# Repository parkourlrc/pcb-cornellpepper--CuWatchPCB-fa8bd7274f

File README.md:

# Pepper-V2
V2 pepper PCB test

## Changes for Rev-3
- Replace the SWD and SWCLK on J7 with some I2C and UART capable GPIOs from Pico. The SWD and SWCLK weren't connected in Rev2 the way I thought they would be
- Replace TMP36 temperature sensor with a TMP235A (similar but cheaper)
- add ability to turn off SiPM 30V from Pico
- make test poinst 1.2mm in diameter (were 0.7mm)
- add logos (woo hoo) and CPERL/CLASSE names

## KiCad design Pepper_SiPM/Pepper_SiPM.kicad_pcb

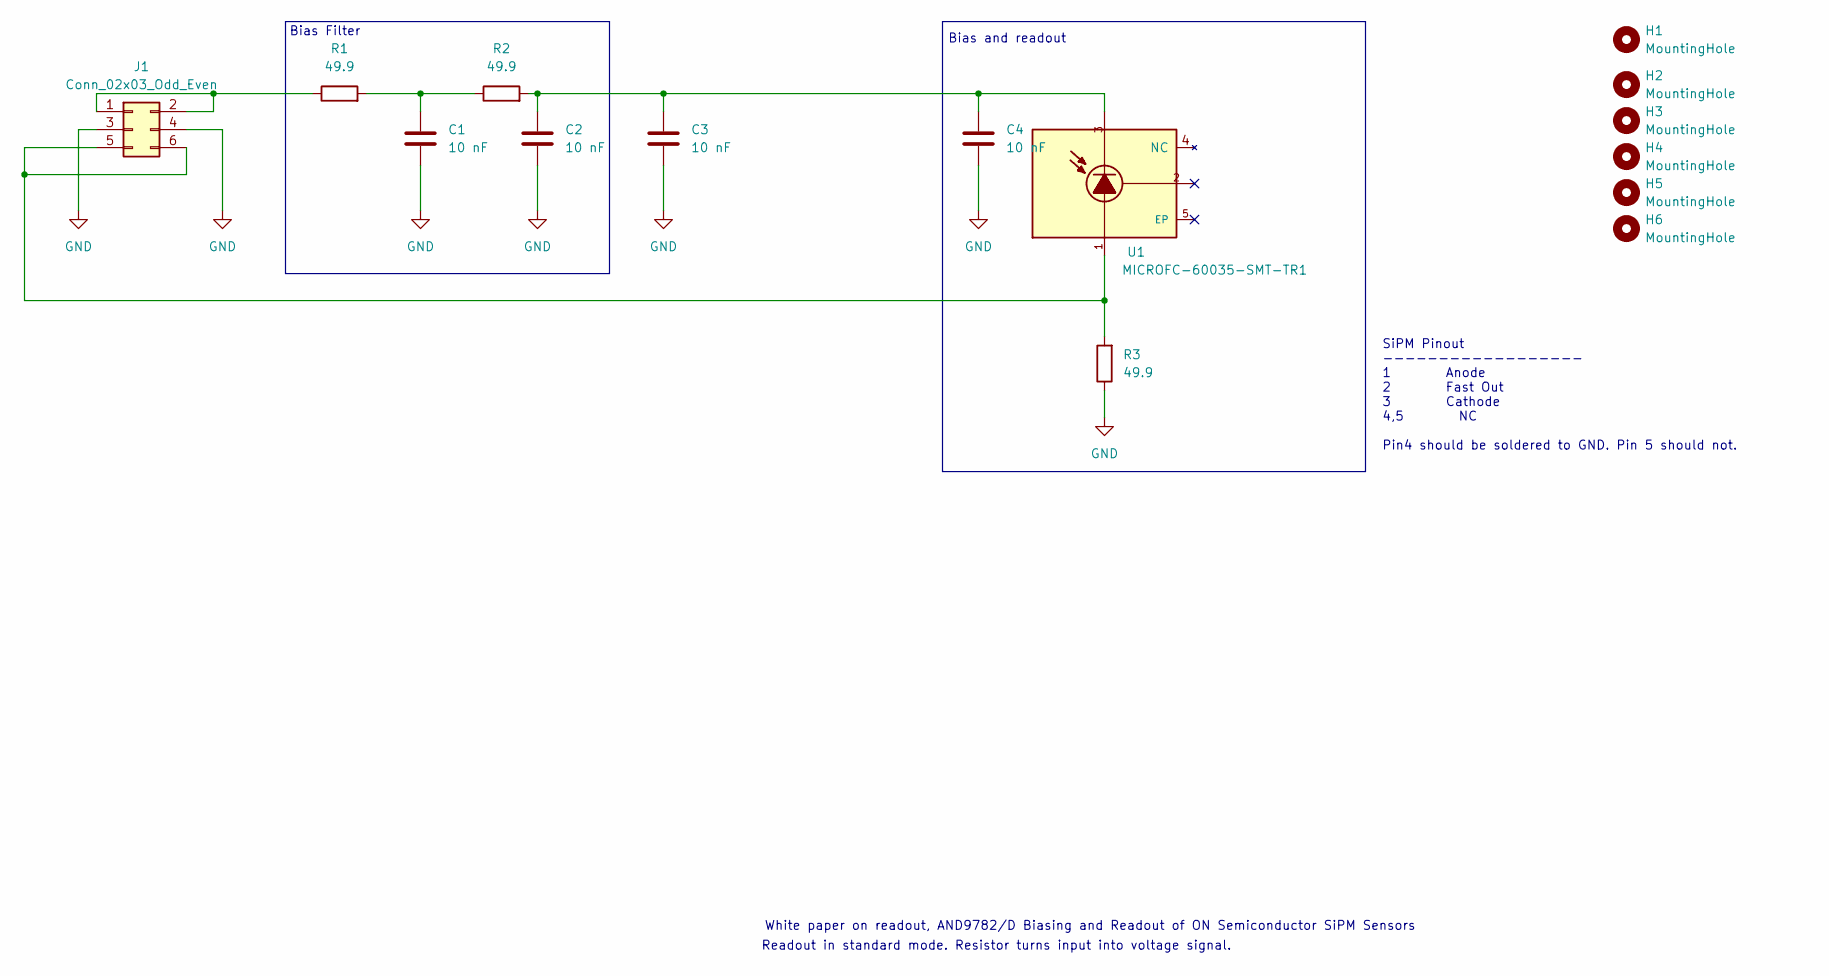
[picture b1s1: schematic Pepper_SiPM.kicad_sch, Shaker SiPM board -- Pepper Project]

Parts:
C1, C2, C3, C4: 10 nF; C_0805_2012Metric_Pad1.18x1.45mm_HandSolder
H1, H2, H3, H4, H5, H6: MountingHole; MountingHole_2.2mm_M2_DIN965_Pad_TopBottom
J1: Conn_02x03_Odd_Even; PinHeader_2x03_P2.54mm_Vertical_SMD
R1, R2, R3: 49.9; R_0805_2012Metric_Pad1.20x1.40mm_HandSolder
U1: MICROFC-60035-SMT-TR1; XDCR_MICROFC-60035-SMT-TR1; PARTREV 31 JUL 2018

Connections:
GND: C1.2, C2.2, C3.2, C4.2, J1.3, J1.4, R3.1
unnamed: C1.1, R1.2, R2.1
unnamed: C2.1, C3.1, C4.1, R2.2, U1.3
unnamed: J1.1, J1.2, R1.1
unnamed: J1.5, J1.6, R3.2, U1.1

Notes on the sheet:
Bias and readout
SiPM Pinout ------------------ 1 Anode 2 Fast Out 3 Cathode 4,5 NC Pin4 should be soldered to GND. Pin 5 should not.
White paper on readout, AND9782/D Biasing and Readout of ON Semiconductor SiPM Sensors
Readout in standard mode. Resistor turns input into voltage signal.
Bias Filter

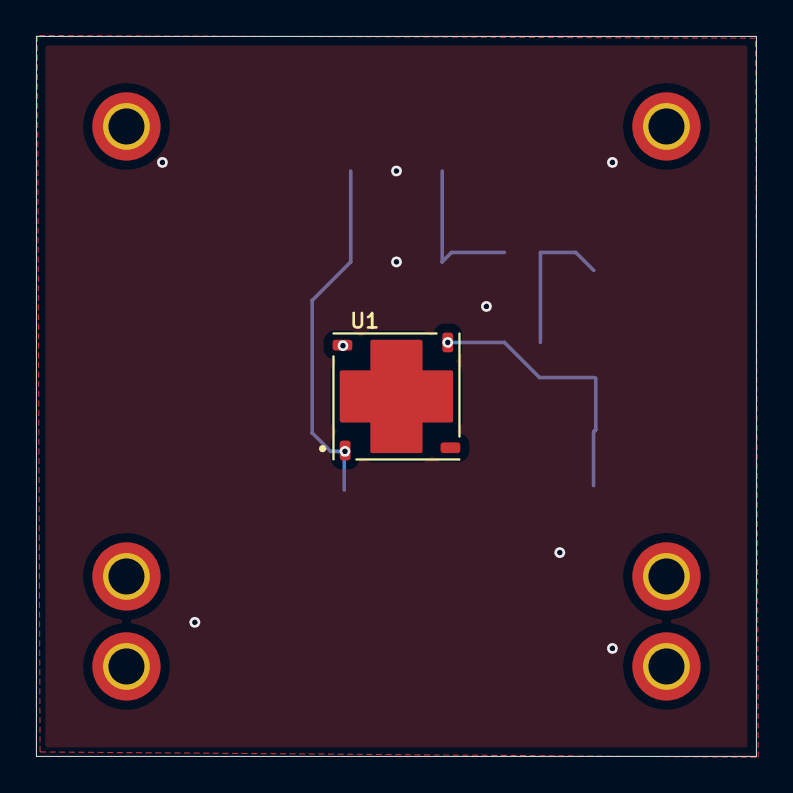
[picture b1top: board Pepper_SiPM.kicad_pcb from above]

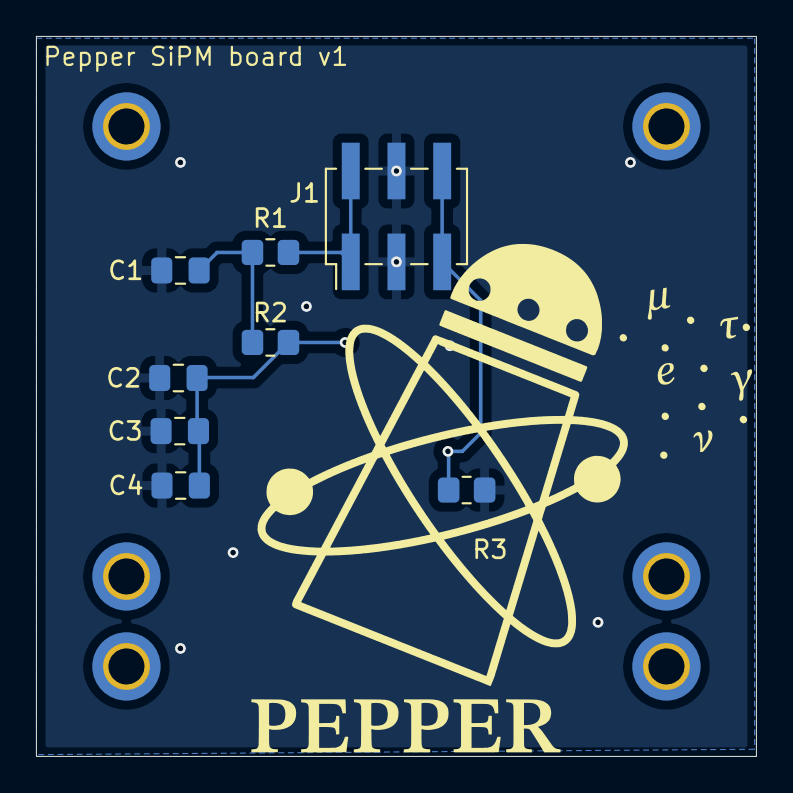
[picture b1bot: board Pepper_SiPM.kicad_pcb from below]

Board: 2 copper layers, 40.0 x 40.0 mm, 15 parts (8 on the bottom side), 5 nets.

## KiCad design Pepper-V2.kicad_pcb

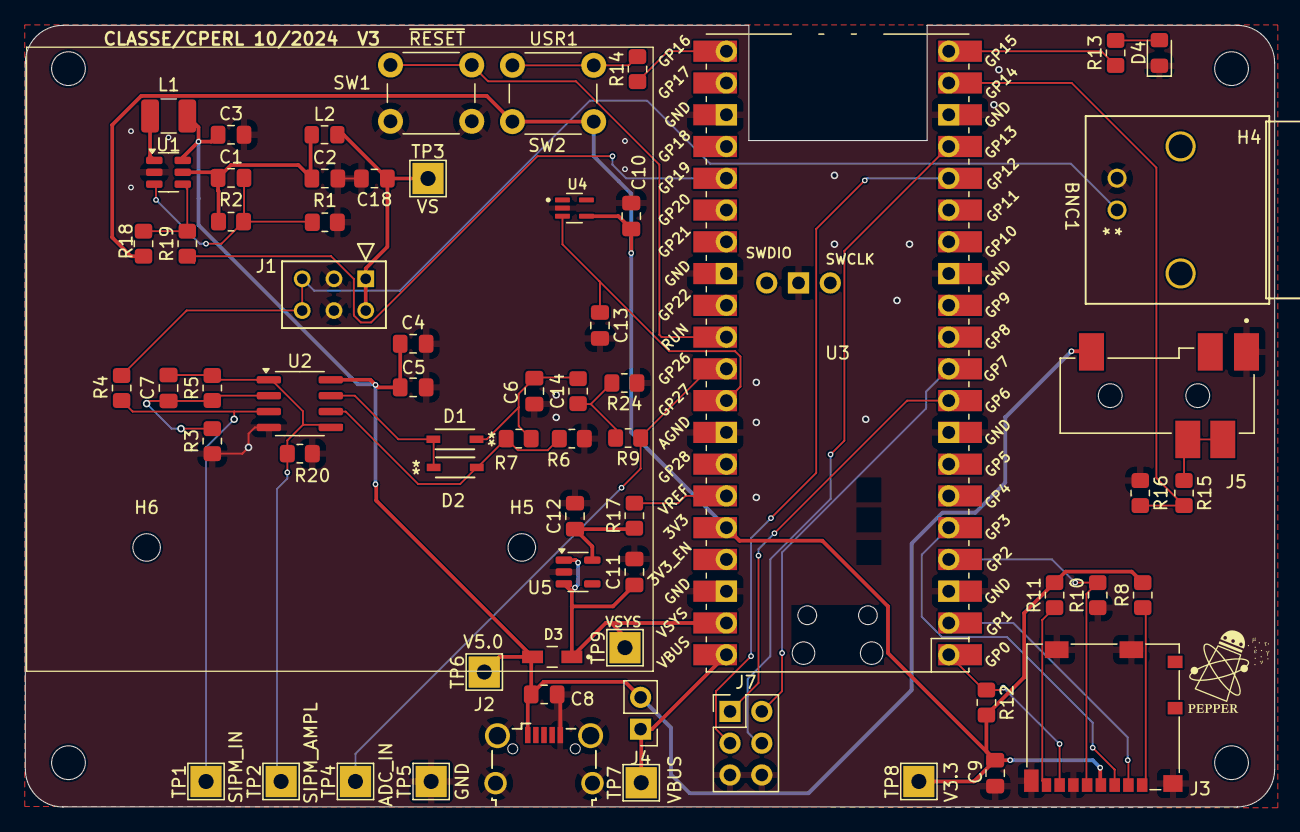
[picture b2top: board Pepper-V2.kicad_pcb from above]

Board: 2 copper layers, 99.9 x 62.5 mm, 71 parts (0 on the bottom side), 40 nets.

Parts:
BNC1: Conn_Coaxial; CONN_73137-5003_MOL
C1: 22 pF; C_0805_2012Metric_Pad1.18x1.45mm_HandSolder
C2: 0.47 uF; C_0805_2012Metric_Pad1.18x1.45mm_HandSolder
C3, C11, C12, C18: 1 uF; C_0805_2012Metric_Pad1.18x1.45mm_HandSolder
C4, C9: 10 uF; C_0805_2012Metric_Pad1.18x1.45mm_HandSolder
C5, C10: 0.1 uF; C_0805_2012Metric_Pad1.18x1.45mm_HandSolder
C6: 20 nF; C_0805_2012Metric_Pad1.18x1.45mm_HandSolder
C7: 10.0 pF; C_0805_2012Metric_Pad1.18x1.45mm_HandSolder
C8: 4.7 uF; C_0805_2012Metric_Pad1.18x1.45mm_HandSolder
C13: 680 pF; C_0805_2012Metric_Pad1.18x1.45mm_HandSolder
C14: 0; R_0805_2012Metric_Pad1.20x1.40mm_HandSolder
D1, D2: MBR0540; SOD123_FAS
D3: MBR1020VL; DIOM3616X98N
D4: LED; LED_0805_2012Metric_Pad1.15x1.40mm_HandSolder
H1, H2, H3, H4: MountingHole; MountingHole_2.7mm_M2.5
H5, H6: MountingHole; MountingHole_2.2mm_M2
J1: Conn_02x03_Odd_Even; CONN_68683-303LF_AMP
J2: 629105150521; USB_Micro-B_Wuerth_629105150521_CircularHoles
J3: Micro_SD_Card; microSD_HC_Molex_104031-0811
J4: Conn_01x02; PinHeader_1x02_P2.54mm_Vertical
J5: SJ-43515RS-SMT-TR; CUI_SJ-43515RS-SMT-TR
J7: Conn_02x03_Odd_Even; PinHeader_2x03_P2.54mm_Vertical
L1: 47 uH; L_1210_3225Metric_Pad1.42x2.65mm_HandSolder
L2: 2k Ferrite Bead; L_0805_2012Metric_Pad1.15x1.40mm_HandSolder
R1, R5, R8, R11, R12, R16, R18, R20: 10k; R_0805_2012Metric_Pad1.20x1.40mm_HandSolder
R2: 226k; R_0805_2012Metric_Pad1.20x1.40mm_HandSolder
R3: 249; R_0805_2012Metric_Pad1.20x1.40mm_HandSolder
R4, R15: 1k; R_0805_2012Metric_Pad1.20x1.40mm_HandSolder
R6, R7: 100k; R_0805_2012Metric_Pad1.20x1.40mm_HandSolder
R9, R17, R19: 0; R_0805_2012Metric_Pad1.20x1.40mm_HandSolder
R10: DNF; R_0805_2012Metric_Pad1.20x1.40mm_HandSolder
R13: 390; R_0805_2012Metric_Pad1.20x1.40mm_HandSolder
R14: 330; R_0805_2012Metric_Pad1.20x1.40mm_HandSolder
R24: 24.9k; R_0805_2012Metric_Pad1.20x1.40mm_HandSolder
SW1: ~{RESET}; SW_PUSH_6mm
SW2: USR1; SW_PUSH_6mm
TP1: SIPM_IN; TestPoint_THTPad_2.5x2.5mm_Drill1.2mm
TP2: SIPM_AMPL; TestPoint_THTPad_2.5x2.5mm_Drill1.2mm
TP3: VS; TestPoint_THTPad_2.5x2.5mm_Drill1.2mm
TP4: ADC_IN; TestPoint_THTPad_2.5x2.5mm_Drill1.2mm
TP5: GND; TestPoint_THTPad_2.5x2.5mm_Drill1.2mm
TP6: V5.0; TestPoint_THTPad_2.5x2.5mm_Drill1.2mm
TP7: VBUS; TestPoint_THTPad_2.5x2.5mm_Drill1.2mm
TP8: V3.3; TestPoint_THTPad_2.5x2.5mm_Drill1.2mm
TP9: VSYS; TestPoint_THTPad_2.5x2.5mm_Drill1.2mm
U1: LT3461; TSOT-23-6
U2: LT1807IS8#PBF; SOIC-8_3.9x4.9mm_P1.27mm
U3: PicoW; RPi_PicoW_SMD_TH
U4: TMP235A4DCKR; SOT65P210X110-5N
U5: TLV70030_SOT23-5; SOT-23-5

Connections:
+3V0: C12.1, R17.1, U5.5 (OUT)
+3V3: C9.1, C10.1, J3.4 (VDD), R8.2, R11.2, R12.2, R18.2, SW2.2, TP8.1, U3.36 (3V3), U4.4 (VDD)
+5V: C3.1, C4.1, C5.1, C8.1, D3.2 (A), J2.1 (VBUS), J4.2, J5.2, L1.1, TP6.1, U1.6 (VIN), U2.8 (V+)
/+3V0_2: R17.2, U3.35 (ADC_VREF)
/COINC: R15.2, R16.2, U3.19 (GPIO14)
/GPIO12: J7.3, U3.16 (GPIO12)
/GPIO13: J7.4, U3.17 (GPIO13)
/LED: R13.1, U3.20 (GPIO15)
/RUN: SW1.1, U3.30 (RUN)
/SIPM_AMPL: C7.2, R5.2, R20.1, TP2.1, U2.1 (O), U2.5 (+)
/SIPM_IN: R4.2, TP1.1, U2.3 (+)
/SIPM_IN_1: BNC1.1 (In), J1.5, J1.6, R4.1
/SIPM_PEAK: C6.1, C14.2, D1.1 (K), R7.2
/SPIO_RX: J3.7 (DAT0), R12.1, U3.1 (GPIO0)
/SPIO_SCK: J3.5 (CLK), R10.2, U3.4 (GPIO2)
/SPIO_TX: J3.3 (CMD), U3.5 (GPIO3)
/UART_RX: J7.2, U3.10 (GPIO7)
/UART_TX: J7.1, U3.9 (GPIO6)
/USR_BUTTON1: R14.1, U3.21 (GPIO16)
/VSYS: C11.1, D3.1 (K), TP9.1, U3.39 (VSYS), U5.1 (IN), U5.3 (EN)
/~SHDN: R18.1, R19.2, U1.4 (~SHDN)
/~SPIO_CS: J3.2 (DAT3/CD), U3.2 (GPIO1)
ADC_IN: R9.1, TP4.1, U3.31 (GPIO26_ADC0)
A_TEMP: C13.1, U3.32 (GPIO27_ADC1), U4.3 (VOUT)
GND: BNC1.2 (Ext), C2.2, C3.2, C4.2, C5.2, C6.2, C8.2, C9.2, C10.2, C11.2, C12.2, C13.2, C18.2, D4.1 (K), J1.3, J1.4, J2.5 (GND), J2.6 (Shield), J3.6 (VSS), J3.11 (SHIELD), J5.1, J7.5, J7.6, R1.1, R3.1, R6.2, R10.1, R16.1, R20.2, R24.1, SW1.2, TP5.1, U1.2 (GND), U2.4 (V-), U3.3 (GND), U3.8 (GND), U3.13 (GND), U3.18 (GND), U3.23 (GND), U3.28 (GND), U3.33 (AGND), U3.38 (GND), U3.42 (GND), U4.2 (GND), U5.2 (GND)
unnamed: C14.1, R9.2, R24.2
unnamed: D1.2 (A), D2.1 (K), U2.7 (O)
unnamed: D2.2 (A), R6.1, R7.1, U2.6 (-)
unnamed: D4.2 (A), R13.2
unnamed: J3.8 (DAT1), R11.1
unnamed: J3.1 (DAT2), R8.1
unnamed: J5.3, J5.6, R15.1
unnamed: R14.2, SW2.1
unnamed: C1.2, R1.2, R2.1, U1.3 (FB)
unnamed: L1.2, U1.1 (SW)
unnamed: C1.1, C2.1, L2.1, R2.2, U1.5 (VOUT)
unnamed: C7.1, R3.2, R5.1, U2.2 (-)
unnamed: R19.1, U3.25 (GPIO19)
VBUS: J4.1, TP7.1, U3.40 (VBUS)
VS: C18.1, J1.1, J1.2, L2.2, TP3.1

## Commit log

2024-08-11 initial commit of repo
2024-08-12 checkpoint
2024-08-14 as sent to pcbnow
2024-08-22 interim updates
2024-08-23 full BOM annotation
2024-08-23 final version for BOM with BOM XLSX file
2024-08-27 refining parts list
2024-08-27 oops
2024-08-29 fix bom mistake
2024-09-05 picow -> picow h
2024-10-25 updates to latest Rev
2024-10-25 updates for v3
2024-11-14 fix footprint for U2 (LT1807)
2024-12-11 as built schematic PDF and Shaker name on drawing
2026-02-13 add SiPM board first pass
